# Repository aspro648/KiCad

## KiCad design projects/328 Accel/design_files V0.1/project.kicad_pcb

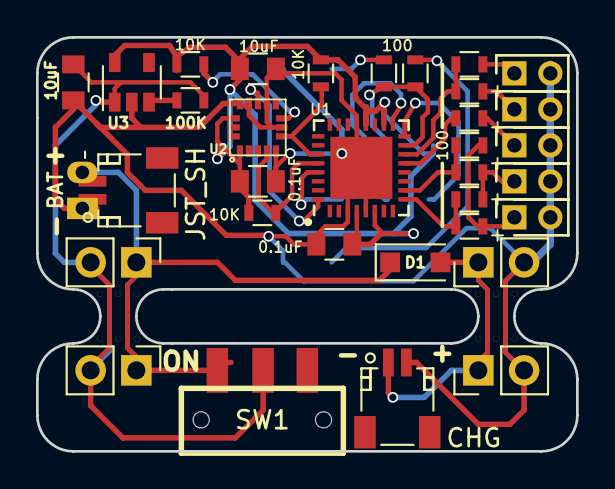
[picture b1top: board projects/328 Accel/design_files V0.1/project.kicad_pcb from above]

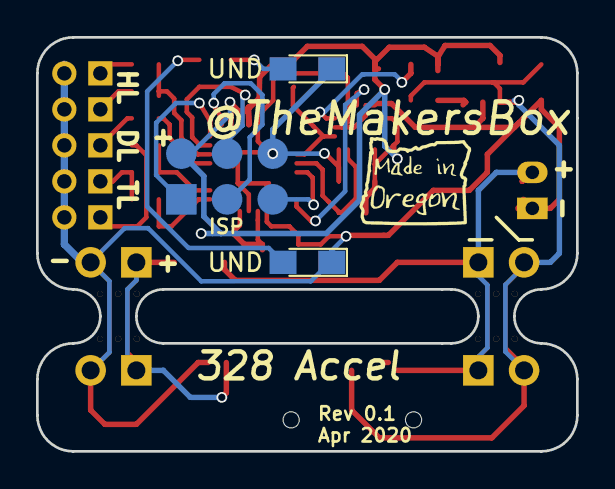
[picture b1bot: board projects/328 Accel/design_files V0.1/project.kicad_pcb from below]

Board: 2 copper layers, 30.0 x 23.0 mm, 38 parts (3 on the bottom side), 25 nets.

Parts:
C1, C4: 10uF; C_0805
C2, C3: 0.1uF; C_0805
CON1: ISP; Pin_Header_Straight_2x03_Pitch2.54mm
D1: D; D_SOD-123F
D4, D5: UND; LED_0805_HandSoldering
J1, J6: HL; PIN_HEADER_LED
J2: CHG; JST_SH_SM02B-SRSS-TB_02x1.00mm_Angled
J3: BAT; JST_SH_SM02B-SRSS-TB_02x1.00mm_Angled
J4, J5, J44, J55: CONN; Pin_Header_Straight_1x02_Pitch2.54mm
J7, J8: TL; PIN_HEADER_LED
J9: DSH; PIN_HEADER_LED
J10: JST_PH; JST_PH_S2B-PH-K_02x2.00mm_Angled
R1, R2, R3: 10K; R_0603
R4, R5, R6, R7, R8, R9, R10, R11, R12: 100; R_0603
R13: 100K; R_0603
SW1: SW_SPDT; SPST_SMD
U1: ATMEGA328-MU; QFN-32-1EP_5x5mm_Pitch0.5mm
U2: LIS3DH; LIS3DH_EP
U3: MIC5225-3.3; SOT-23-5
VAL: MadeInOregonRev25

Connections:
+BATT: C4.1, J4.2, J44.2, R13.1, SW1.2, U3.1
/D2: U1.32, U2.11
/D5: R4.1, R9.1, U1.9
/D6: R5.1, R8.1, U1.10
/D9: R10.1, U1.13
/D10: R6.1, R7.1, U1.14
/MISO: CON1.1, U1.16
/MOSI: CON1.4, R11.1, R12.1, U1.15
/SCK: CON1.3, U1.17
/SCL: R3.2, U1.28, U2.4
/SDA: R2.2, U1.27, U2.6
/~CS: R1.2, U2.8
/~RESET: CON1.5, U1.29
GND: C1.2, C2.2, C3.2, C4.2, CON1.6, D4.1, D5.1, J1.2, J2.2, J3.1, J5.2, J6.2, J7.2, J8.2, J9.2, J10.1, J55.2, U1.3, U1.5, U1.21, U2.5, U2.7, U2.10, U2.12, U2.13, U3.2
unnamed: D1.1, J3.2, J4.1, J10.2, J44.1, SW1.1
unnamed: D1.2, J2.1, J5.1, J55.1
unnamed: D4.2, R11.2
unnamed: D5.2, R12.2
unnamed: J1.1, R6.2
unnamed: J6.1, R7.2
unnamed: J7.1, R4.2, R8.2
unnamed: J8.1, R5.2, R9.2
unnamed: J9.1, R10.2
unnamed: R13.2, U3.3
VCC: C1.1, C2.1, C3.1, CON1.2, R1.1, R2.1, R3.1, U1.4, U1.6, U1.18, U1.20, U2.1, U2.14, U3.5

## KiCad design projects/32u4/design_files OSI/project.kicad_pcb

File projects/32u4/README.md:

32U4
----------------

Intro

Bill Of Materials
----------------
  
- 1 ea., Perfect Purple PCB from OSH Park, with not so perfect layout from [design_files](design_files/) folder.
- U1, ATMEGA32U4-AU, IC MCU 8BIT 32KB FLASH 44TQFP, https://www.digikey.com/short/jb25pc
- U2, IC REG LINEAR 3.3V 150MA SOT23-5, MIC5225-3.3YM5-TR, https://www.digikey.com/short/jb2rq8
- SW1, TACTILE KMR231NG LFS, https://www.digikey.com/short/jb2r5m
- U3, IC BUFFER NON-INVERT 5.5V 5TSOP SOT-753, 74HCT1G125GV,125 https://www.digikey.com/short/jb2f3p
- Y1, Resonator 8MHZ, CSTNE8M00G55Z000R0, https://www.digikey.com/short/jb22j1
or
  Y1, CER RES 8.0000MHZ 30PF SMD, PBRC8.00HR50X000 7.40mm x 3.40mm

- D1, D4, DIODE SCHOTTKY 20V 1A SOD123FL, MBR120VLSFT3GOSCT-ND, https://www.digikey.com/short/jb22rn 
- C6, C8, C9, 10uF SMD 0805, https://www.digikey.com/short/j5d39w 
- C7, C14 1uF SMD 0603, https://www.digikey.com/short/j5d397
- X3, CONN RCPT MICRO USB R/A SMD, Molex 1050170001, https://www.digikey.com/short/jb2205
100K ohm 0603 SMD resistor, https://www.digikey.com/short/j5d3b3

Design Files
----------------
This project is designed using Open Source [KiCad](http://kicad-pcb.org/). Design files are located in the [design_files](design_files/) folder.  You can oogle the [schematic](docs/project.sch.pdf).

Firmware
----------------
TBD

Assembly Instructions
----------------
TBD

License
----------------
[Attribution-ShareAlike 3.0 United States (CC BY-SA 3.0 US)](https://creativecommons.org/licenses/by-sa/3.0/us/)

You are free to:

- Share — copy and redistribute the material in any medium or format
- Adapt — remix, transform, and build upon the material

Under the following terms:

- Attribution — You must give appropriate credit, provide a link to the license, and indicate if changes were made. You may do so in any reasonable manner, but not in any way that suggests the licensor endorses you or your use.
- ShareAlike — If you remix, transform, or build upon the material, you must distribute your contributions under the same license as the original.

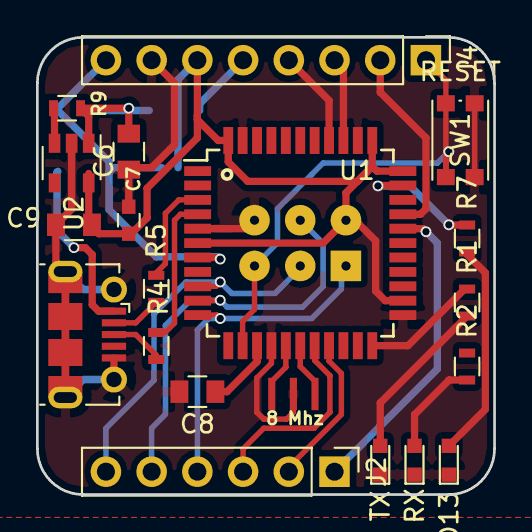
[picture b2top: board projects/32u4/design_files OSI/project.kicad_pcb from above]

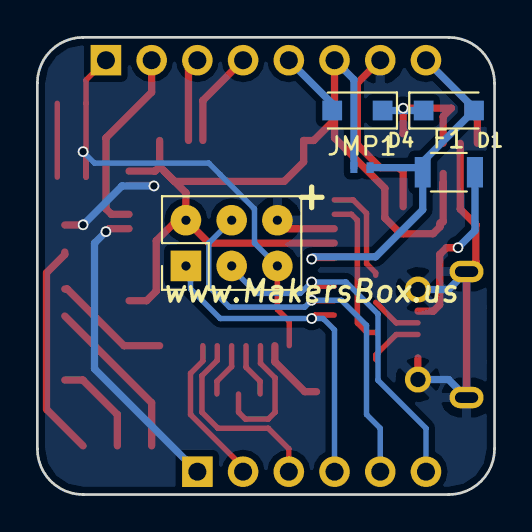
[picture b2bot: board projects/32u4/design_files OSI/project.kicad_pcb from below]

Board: 2 copper layers, 25.4 x 25.4 mm, 25 parts (5 on the bottom side), 29 nets.

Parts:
C6, C8, C9: 10uF; C_0805
C7: 1uF; C_0603
CON1: AVR-ISP-6; Pin_Header_Straight_2x03_Pitch2.54mm
D1, D4: MBR120; D_SOD-123F
D3: TX; LED_0603
D5: RX; LED_0603
D13: D13; LED_0603
F1: Polyfuse; R_1206
J2: Conn_01x06; Pin_Header_Straight_1x06_Pitch2.54mm
J4: Conn_01x08; Pin_Header_Straight_1x08_Pitch2.54mm
JMP1: DNP; R_0402_NoSilk
R1, R2, R7: 180; R_0603
R4, R5: 22; R_0603
R9: 100K; R_0603
SW1: RESET; SW_SPST_KMR2
U1: ATMEGA32U4-AU; TQFP-44_10x10mm_Pitch0.8mm
U2: MIC5225-3.3; SOT-23-5
X3: USB_OTG; USB_Micro-B_Molex-105017-0001
Y1: 8 Mhz; Resonator_SMD_CTSC_1.3mmx3.2mm

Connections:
+BATT: D4.2, J4.5
/A0: J4.3, U1.36
/A1: J4.4, U1.37
/D9: J2.1, U1.29
/D10: J4.2, U1.30
/D13: R7.2, U1.32
/D+: R4.1, U1.4
/D-: R5.1, U1.3
/MISO: CON1.1, J2.4, U1.11
/MOSI: CON1.4, J2.5, U1.10
/RXLED: R2.2, U1.8
/SCK: CON1.3, J2.6, U1.9
/SCL: J2.3, U1.18
/SDA: J2.2, U1.19
/TXLED: R1.2, U1.22
/VHI: C6.1, D1.1, D4.1, R9.2, U2.1
/~RESET: CON1.5, J4.1, SW1.2, U1.13
GND: C6.2, C7.2, C8.2, C9.2, CON1.6, D3.1, D5.1, D13.1, J4.7, SW1.1, U1.5, U1.15, U1.23, U1.35, U1.43, U2.2, X3.5, X3.6, Y1.2
unnamed: D3.2, R1.1
unnamed: D5.2, R2.1
unnamed: D13.2, R7.1
unnamed: F1.2, X3.1
unnamed: R4.2, X3.3
unnamed: R5.2, X3.2
unnamed: R9.1, U2.3
unnamed: U1.16, Y1.3
unnamed: U1.17, Y1.1
VBUS: D1.2, F1.1, J4.8, JMP1.2, U1.7
VCC: C7.1, C8.1, C9.1, CON1.2, J4.6, JMP1.1, U1.6, U1.14, U1.24, U1.33, U1.34, U1.44, U2.5

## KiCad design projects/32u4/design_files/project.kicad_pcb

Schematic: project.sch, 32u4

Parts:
C6, C8, C9: 10uF; C_0805
C7: 1uF; C_0603
CON1: AVR-ISP-6; Pin_Header_Straight_2x03_Pitch2.54mm
D1, D4: MBR120; D_SOD-123F
D2: D13; LED_0603
D3: TX; LED_0603
D5: RX; LED_0603
J2, J4: Conn_01x14; Pin_Header_Straight_1x14_Pitch2.54mm
R1, R2, R7: 180; R_0603
R4, R5: 22; R_0603
R9: 100K; R_0603
SW1: RESET; SW_SPST_KMR2
SW2: D4; SW_SPST_KMR2
U1: ATMEGA32U4-AU; TQFP-44_10x10mm_Pitch0.8mm
U2: MIC5225-3.3; SOT-23-5
U3: 74HCT1G125; TSOP-5_1.65x3.05mm_Pitch0.95mm
X3: USB_OTG; USB_Micro-B_Molex-105017-0001
Y1: 8 Mhz; Resonator_SMD_CTSC_1.3mmx3.2mm

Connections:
+3V3: C7.1, C8.1, C9.1, CON1.2, J4.3, U1.6 (UCAP), U1.14 (VCC), U1.24 (AVCC), U1.33 ((~HWB~)PE2), U1.34 (VCC), U1.44 (AVCC), U2.5 (OUT)
+BATT: D4.2 (A), J4.4
/A0: J2.6, U1.36 ((ADC7/TDI)PF7)
/A1: J2.5, U1.37 ((ADC6/TDO)PF6)
/A2: J2.4, U1.38 ((ADC5/TMS)PF5)
/A3: J2.3, U1.39 ((ADC4/TCK)PF4)
/A4: J2.2, U1.40 ((ADC1)PF1)
/A5: J2.1, U1.41 ((ADC0)PF0)
/AREF: U1.42 (AREF)
/D0: J2.12, U1.20 ((RXD/INT2)PD2)
/D1: J2.11, U1.21 ((TXD/INT3)PD3)
/D4: J2.10, SW2.1, U1.25 ((ICP2/ADC8)PD4)
/D5: U1.31 ((OC3A/~OC4A~)PC6), U3.2
/D5_5V: J4.5, U3.4
/D6: J2.7, U1.27 ((T0/OC4D/ADC10)PD7)
/D7: U1.1 ((INT6/AIN0)PE6)
/D8: J4.12, U1.28 ((ADC11/PCINT4)PB4)
/D9: J4.13, U1.29 ((ADC12/OC1A/~OC4B~/PCINT12)PB5)
/D10: J4.14, U1.30 ((ADC13/OC1B/OC4B/PCINT13)PB6)
/D11: J4.10, U1.12 ((OC0A/OC1C/~RTS~/PCINT7)PB7)
/D12: J2.8, U1.26 ((T1/~OC4D~/ADC9)PD6)
/D13: R7.2, U1.32 ((ICP3/CLK0/OC4A)PC7)
/MISO: CON1.1, J4.9, U1.11 ((PDO/MISO/PCINT3)PB3)
/MOSI: CON1.4, J4.8, U1.10 ((PDI/MOSI/PCINT2)PB2)
/RXLED: J4.6, R2.2, U1.8 ((SS/PCINT0)PB0)
/SCK: CON1.3, J4.7, U1.9 ((SCLK/PCINT1)PB1)
/SCL: J2.14, U1.18 ((OC0B/SCL/INT0)PD0)
/SDA: J2.13, U1.19 ((SDA/INT1)PD1)
/TXLED: J2.9, R1.2, U1.22 ((XCK1/~CTS~)PD5)
/VHI: C6.1, D1.1 (K), D4.1 (K), R9.2, U2.1 (IN), U3.5 (VCC)
/~RESET: CON1.5, J4.11, SW1.2, U1.13 (~RESET~)
GND: C6.2, C7.2, C8.2, C9.2, CON1.6, D2.1 (K), D3.1 (K), D5.1 (K), J4.1, SW1.1, SW2.2, U1.5 (UGND), U1.15 (GND), U1.23 (GND), U1.35 (GND), U1.43 (GND), U2.2 (GND), U3.1 (~OE), U3.3 (GND), X3.5 (GND), X3.6 (Shield), Y1.2
unnamed: D2.2 (A), R7.1
unnamed: D3.2 (A), R1.1
unnamed: D5.2 (A), R2.1
unnamed: R4.1, U1.4 (D+)
unnamed: R4.2, X3.3 (D+)
unnamed: R5.1, U1.3 (D-)
unnamed: R5.2, X3.2 (D-)
unnamed: R9.1, U2.3 (EN)
unnamed: U1.16 (XTAL2), Y1.3
unnamed: U1.17 (XTAL1), Y1.1
VBUS: D1.2 (A), J4.2, U1.7 (VBUS), X3.1 (VBUS)

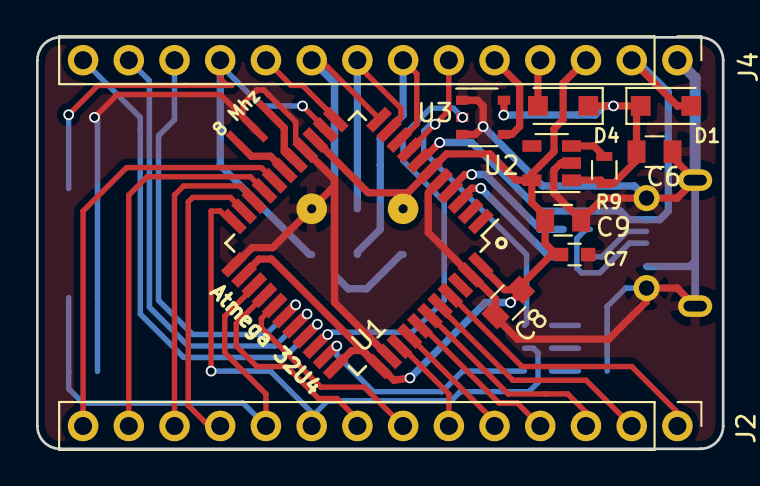
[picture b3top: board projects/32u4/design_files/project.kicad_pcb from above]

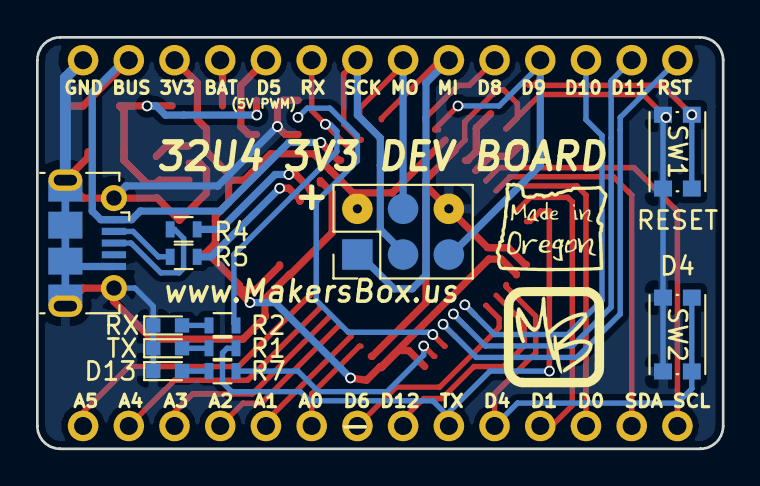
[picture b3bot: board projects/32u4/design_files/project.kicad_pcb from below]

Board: 2 copper layers, 38.1 x 22.9 mm, 27 parts (12 on the bottom side), 41 nets.

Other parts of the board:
VAL: MB225rev
VAL#2: MadeInOregonRev25

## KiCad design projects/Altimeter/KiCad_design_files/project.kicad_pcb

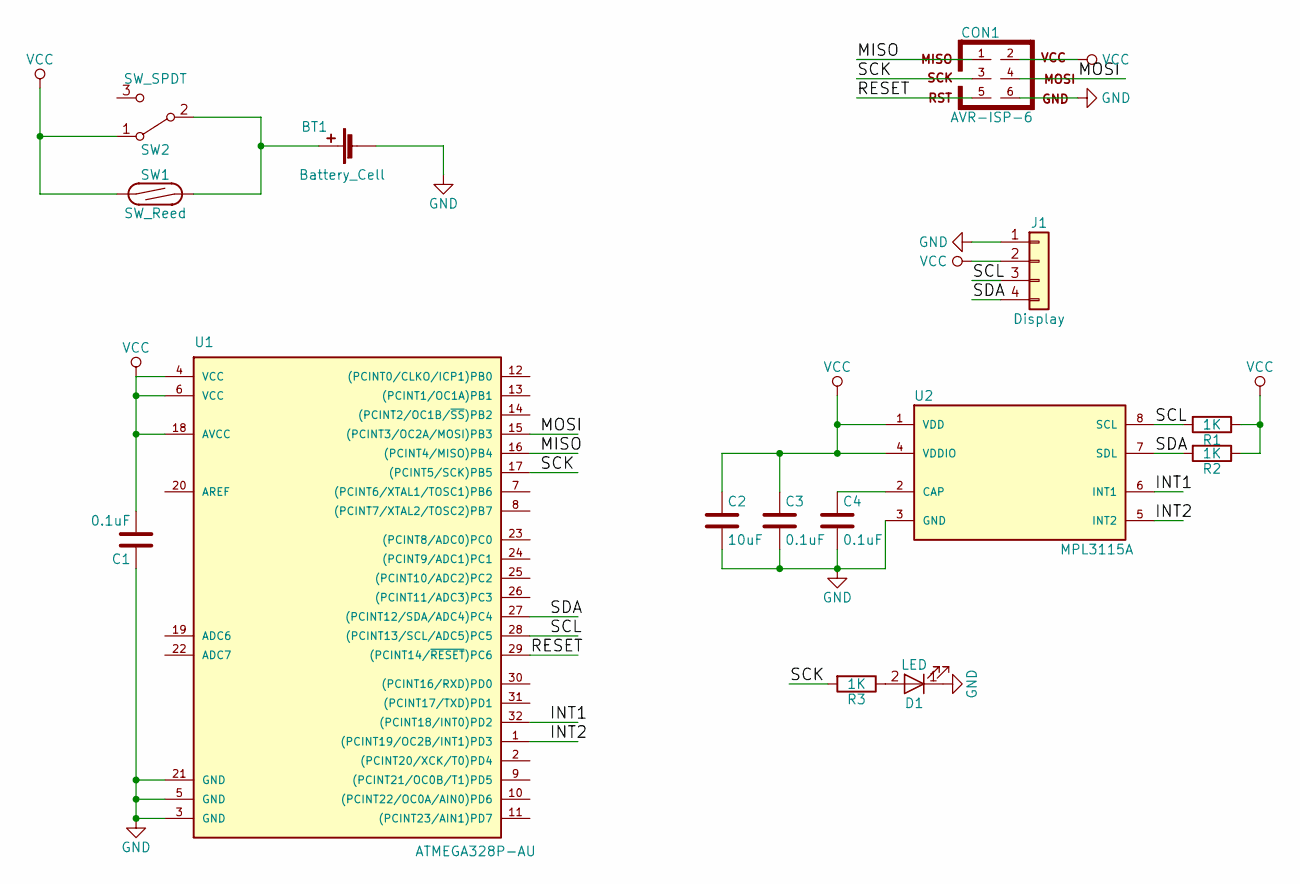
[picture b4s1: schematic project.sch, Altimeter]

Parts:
BT1: Battery_Cell; BATT_CR2032_SMD
C1, C3, C4: 0.1uF; C_0805
C2: 10uF; C_1206
CON1: AVR-ISP-6
D1: LED; LED_0805
J1: Display; Pin_Header_Straight_1x04_Pitch2.54mm
R1, R2, R3: 1K; R_0805
SW1: SW_Reed; REED_SWITCH
SW2: SW_SPDT; SW_SPDT_CK-JS102011SAQN
U1: ATMEGA328P-AU; TQFP-32_7x7mm_Pitch0.8mm
U2: MPL3115A; LGA-8_3x5mm_Pitch1.25mm

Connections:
/INT1: U1.32 ((PCINT18/INT0)PD2), U2.6 (INT1)
/INT2: U1.1 ((PCINT19/OC2B/INT1)PD3), U2.5 (INT2)
/MISO: CON1.1, U1.16 ((PCINT4/MISO)PB4)
/MOSI: CON1.4, U1.15 ((PCINT3/OC2A/MOSI)PB3)
/RESET: CON1.5, U1.29 ((PCINT14/~RESET~)PC6)
/SCK: CON1.3, R3.2, U1.17 ((PCINT5/SCK)PB5)
/SCL: J1.3, R1.2, U1.28 ((PCINT13/SCL/ADC5)PC5), U2.8 (SCL)
/SDA: J1.4, R2.2, U1.27 ((PCINT12/SDA/ADC4)PC4), U2.7 (SDL)
GND: BT1.2 (-), C1.1, C2.2, C3.2, C4.2, CON1.6, D1.1 (K), J1.1, U1.3 (GND), U1.5 (GND), U1.21 (GND), U2.3 (GND)
unnamed: BT1.1 (+), SW1.2, SW2.2 (B)
unnamed: C4.1, U2.2 (CAP)
unnamed: D1.2 (A), R3.1
VCC: C1.2, C2.1, C3.1, CON1.2, J1.2, R1.1, R2.1, SW1.1, SW2.1 (A), U1.4 (VCC), U1.6 (VCC), U1.18 (AVCC), U2.1 (VDD), U2.4 (VDDIO)

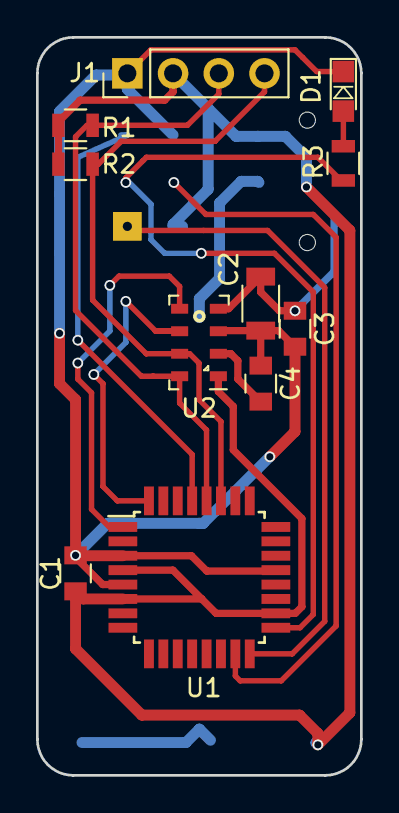
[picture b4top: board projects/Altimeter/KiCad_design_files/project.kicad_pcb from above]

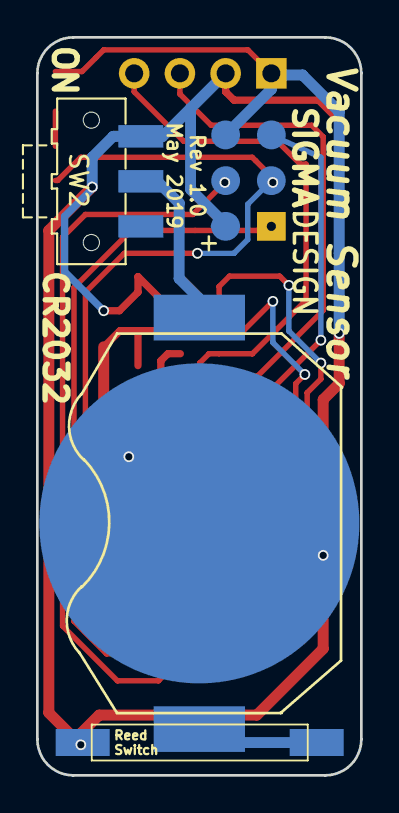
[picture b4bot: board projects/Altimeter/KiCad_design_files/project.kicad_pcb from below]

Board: 2 copper layers, 18.0 x 41.0 mm, 15 parts (4 on the bottom side), 13 nets.
